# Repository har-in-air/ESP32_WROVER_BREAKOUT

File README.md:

# ESP32_WROVER_BREAKOUT

## Features
* Breadboard compatible connector spacing
* TPS82140  switched-mode power supply - Vinmax 17V, Vout 3.3V @ max 2A, Iq ~20uA 
* TPS3839 voltage supervisor keeps ESP32 in reset if supply voltage drops below threshold. This is useful when you have a large capacitor on the 3.3V power supply that discharges slowly. Use TPS3839K33DBZ for a voltage threshold of ~2.93V.
* Solder jumper to select between external regulated 3.3V supply or TPS82140 output.
* Schematic and board layout using Kicad 5.0.2 on Ubuntu 18.10 amdx64
* Gerber files generated using instructions at https://support.jlcpcb.com/article/44-how-to-export-kicad-pcb-to-gerber-files
* PCB layout designed for hand soldering
  * vias in pads, no thermal relief on pads. 
  * Use low-temperature solder for TPS82140, this will make it easier and safer to reflow with a DIY process, e.g. electric skillet. 
  * There's no need to risk damage to the ESP32-WROVER module by reflow-soldering it. Just apply thermal grease (not solder paste) on the ESP32-WROVER ground pad before soldering the castellated-edge pins.

## Credits
ESP32-WROVER footprint and component library from https://github.com/aliafshar/esp32-wrover-kicad

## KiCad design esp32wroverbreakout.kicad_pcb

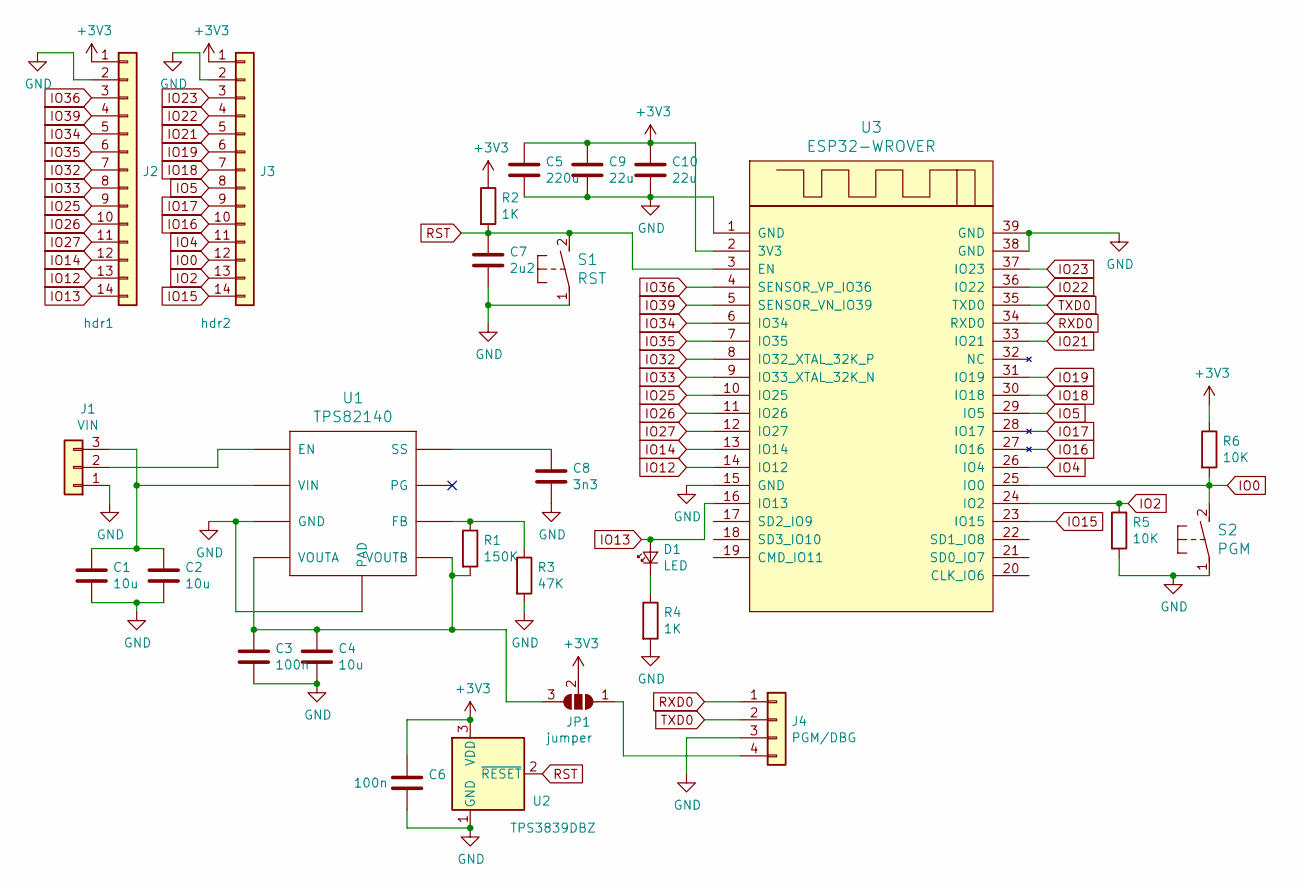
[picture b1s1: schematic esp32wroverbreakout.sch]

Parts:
C1, C2: 10u; C_1206_3216Metric
C3, C6: 100n; C_0603_1608Metric
C4: 10u; C_0805_2012Metric
C5: 220u; CP_EIA-6032-28_Kemet-C
C7: 2u2; C_0805_2012Metric
C8: 3n3; C_0805_2012Metric
C9, C10: 22u; C_1206_3216Metric
D1: LED; LED_0603_1608Metric
J1: VIN; PinSocket_1x03_P2.54mm_Vertical
J2: hdr1; PinSocket_1x14_P2.54mm_Vertical
J3: hdr2; PinSocket_1x14_P2.54mm_Vertical
J4: PGM/DBG; PinSocket_1x04_P2.54mm_Vertical
JP1: jumper; SolderJumper-3_P1.3mm_Open_Pad1.0x1.5mm
R1: 150K; R_0603_1608Metric
R2, R4: 1K; R_0603_1608Metric
R3: 47K; R_0603_1608Metric
R5, R6: 10K; R_0603_1608Metric
S1: RST; DTSM-3
S2: PGM; DTSM-3
U1: TPS82140
U2: TPS3839DBZ; SOT-23
U3: ESP32-WROVER

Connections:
+3V3: C5.1, C6.1, C9.1, C10.1, J2.1, J3.1, JP1.2 (C), R2.1, R6.1, U2.3 (VDD), U3.2 (3V3)
GND: C1.2, C2.2, C3.2, C4.2, C5.2, C6.2, C7.2, C8.2, C9.2, C10.2, J1.1, J2.2, J3.2, J4.3, R3.2, R4.2, R5.2, S1.1, S2.1, U1.P$3 (GND), U1.P$9 (PAD), U2.1 (GND), U3.1 (GND), U3.15 (GND), U3.38 (GND), U3.39 (GND)
IO0: J3.12, R6.2, S2.2, U3.25 (IO0)
IO2: J3.13, R5.1, U3.24 (IO2)
IO4: J3.11, U3.26 (IO4)
IO5: J3.8, U3.29 (IO5)
IO12: J2.13, U3.14 (IO12)
IO13: D1.2 (A), J2.14, U3.16 (IO13)
IO14: J2.12, U3.13 (IO14)
IO15: J3.14, U3.23 (IO15)
IO16: J3.10, U3.27 (IO16)
IO17: J3.9, U3.28 (IO17)
IO18: J3.7, U3.30 (IO18)
IO19: J3.6, U3.31 (IO19)
IO21: J3.5, U3.33 (IO21)
IO22: J3.4, U3.36 (IO22)
IO23: J3.3, U3.37 (IO23)
IO25: J2.9, U3.10 (IO25)
IO26: J2.10, U3.11 (IO26)
IO27: J2.11, U3.12 (IO27)
IO32: J2.7, U3.8 (IO32_XTAL_32K_P)
IO33: J2.8, U3.9 (IO33_XTAL_32K_N)
IO34: J2.5, U3.6 (IO34)
IO35: J2.6, U3.7 (IO35)
IO36: J2.3, U3.4 (SENSOR_VP_IO36)
IO39: J2.4, U3.5 (SENSOR_VN_IO39)
unnamed: C1.1, C2.1, J1.3, U1.P$2 (VIN)
unnamed: C3.1, C4.1, JP1.3 (B), R1.2, U1.P$4 (VOUTA), U1.P$5 (VOUTB)
unnamed: C8.1, U1.P$8 (SS)
unnamed: D1.1 (K), R4.1
unnamed: J1.2, U1.P$1 (EN)
unnamed: J4.4, JP1.1 (A)
unnamed: R1.1, R3.1, U1.P$6 (FB)
RST: C7.1, R2.2, S1.2, U2.2 (~RESET), U3.3 (EN)
RXD0: J4.1, U3.34 (RXD0)
TXD0: J4.2, U3.35 (TXD0)

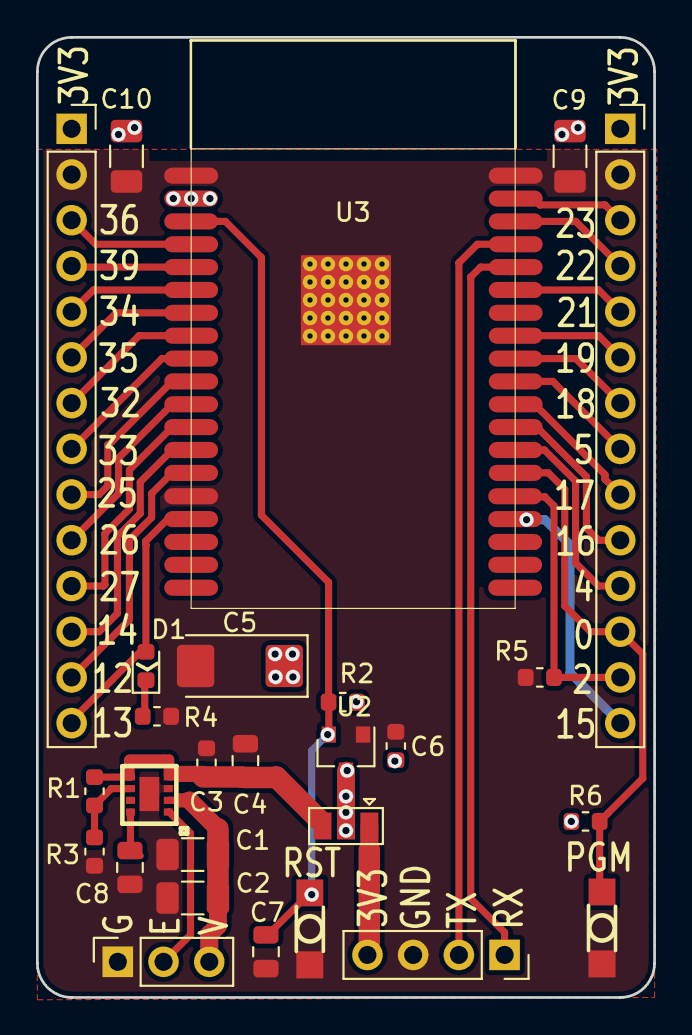
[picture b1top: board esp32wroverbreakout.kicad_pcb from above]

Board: 2 copper layers, 34.3 x 53.3 mm, 27 parts (0 on the bottom side), 36 nets.

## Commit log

2019-01-25 Add files via upload
    Gerber zip file
2019-01-25 Add files via upload
    Kicad 5.0 project, schematic and board files
2019-01-25 Add files via upload
    EasyEDA generated views of PCB top and bottom
